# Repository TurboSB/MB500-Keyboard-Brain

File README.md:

# MB500-Keyboard-Brain
 replacement controller for the Korg SP500 with USB MIDI support using a teensy 4.1.

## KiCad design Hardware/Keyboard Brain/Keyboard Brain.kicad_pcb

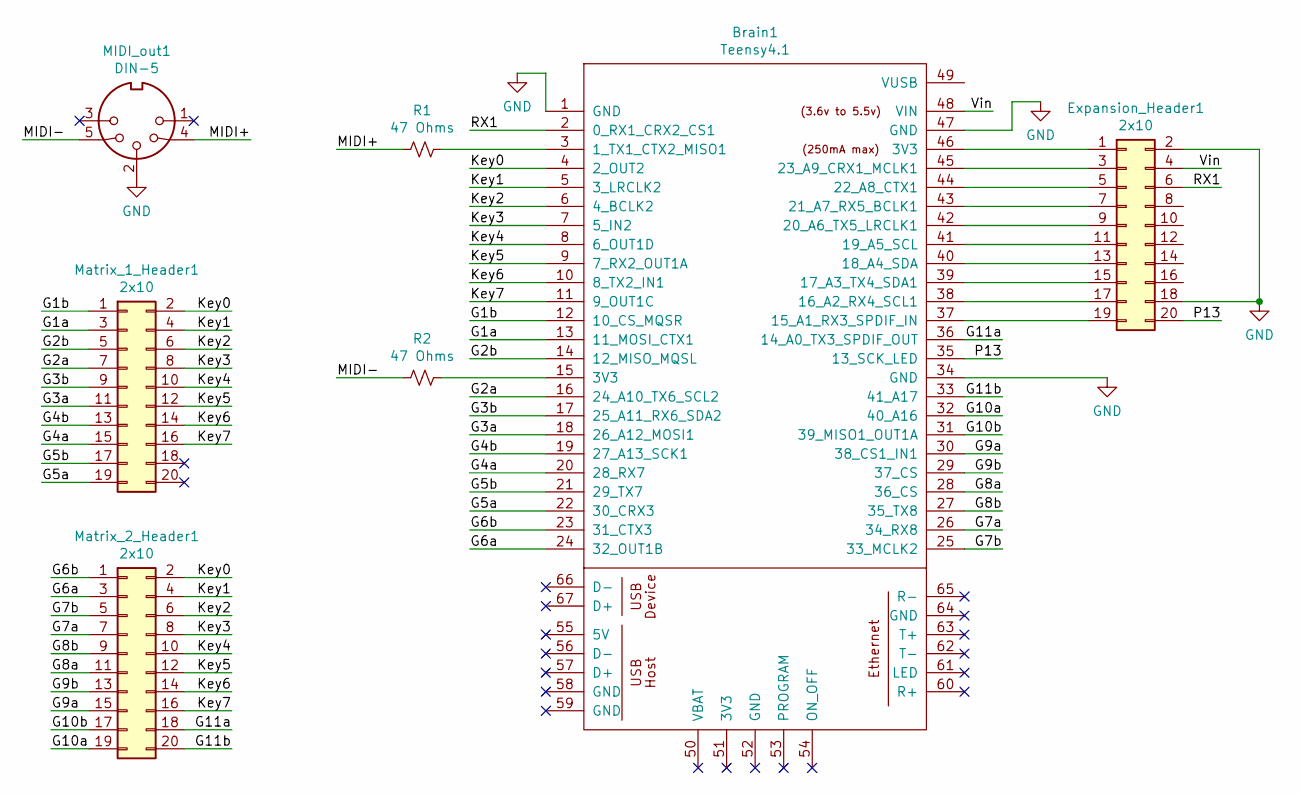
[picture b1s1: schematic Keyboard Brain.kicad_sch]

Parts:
Brain1: Teensy4.1; Teensy41_outer
Expansion_Header1: 2x10; PinHeader_2x10_P2.54mm_Vertical
MIDI_out1: DIN-5; MIDI_DIN5
Matrix_1_Header1, Matrix_2_Header1: 2x10; PinHeader_2x10_P2.54mm_Vertical
R1, R2: 47 Ohms; R_Axial_DIN0411_L9.9mm_D3.6mm_P25.40mm_Horizontal

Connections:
/G1a: Brain1.13 (11_MOSI_CTX1), Matrix_1_Header1.3
/G1b: Brain1.12 (10_CS_MQSR), Matrix_1_Header1.1
/G2a: Brain1.16 (24_A10_TX6_SCL2), Matrix_1_Header1.7
/G2b: Brain1.14 (12_MISO_MQSL), Matrix_1_Header1.5
/G3a: Brain1.18 (26_A12_MOSI1), Matrix_1_Header1.11
/G3b: Brain1.17 (25_A11_RX6_SDA2), Matrix_1_Header1.9
/G4a: Brain1.20 (28_RX7), Matrix_1_Header1.15
/G4b: Brain1.19 (27_A13_SCK1), Matrix_1_Header1.13
/G5a: Brain1.22 (30_CRX3), Matrix_1_Header1.19
/G5b: Brain1.21 (29_TX7), Matrix_1_Header1.17
/G6a: Brain1.24 (32_OUT1B), Matrix_2_Header1.3
/G6b: Brain1.23 (31_CTX3), Matrix_2_Header1.1
/G7a: Brain1.26 (34_RX8), Matrix_2_Header1.7
/G7b: Brain1.25 (33_MCLK2), Matrix_2_Header1.5
/G8a: Brain1.28 (36_CS), Matrix_2_Header1.11
/G8b: Brain1.27 (35_TX8), Matrix_2_Header1.9
/G9a: Brain1.30 (38_CS1_IN1), Matrix_2_Header1.15
/G9b: Brain1.29 (37_CS), Matrix_2_Header1.13
/G10a: Brain1.32 (40_A16), Matrix_2_Header1.19
/G10b: Brain1.31 (39_MISO1_OUT1A), Matrix_2_Header1.17
/G11a: Brain1.36 (14_A0_TX3_SPDIF_OUT), Matrix_2_Header1.18
/G11b: Brain1.33 (41_A17), Matrix_2_Header1.20
/Key0: Brain1.4 (2_OUT2), Matrix_1_Header1.2, Matrix_2_Header1.2
/Key1: Brain1.5 (3_LRCLK2), Matrix_1_Header1.4, Matrix_2_Header1.4
/Key2: Brain1.6 (4_BCLK2), Matrix_1_Header1.6, Matrix_2_Header1.6
/Key3: Brain1.7 (5_IN2), Matrix_1_Header1.8, Matrix_2_Header1.8
/Key4: Brain1.8 (6_OUT1D), Matrix_1_Header1.10, Matrix_2_Header1.10
/Key5: Brain1.9 (7_RX2_OUT1A), Matrix_1_Header1.12, Matrix_2_Header1.12
/Key6: Brain1.10 (8_TX2_IN1), Matrix_1_Header1.14, Matrix_2_Header1.14
/Key7: Brain1.11 (9_OUT1C), Matrix_1_Header1.16, Matrix_2_Header1.16
/MIDI+: MIDI_out1.4, R1.2
/MIDI-: MIDI_out1.5, R2.2
/P13: Brain1.35 (13_SCK_LED), Expansion_Header1.20
/RX1: Brain1.2 (0_RX1_CRX2_CS1), Expansion_Header1.6
/Vin: Brain1.48 (VIN), Expansion_Header1.4
GND: Brain1.1 (GND), Brain1.34 (GND), Brain1.47 (GND), Expansion_Header1.2, Expansion_Header1.18, MIDI_out1.2
unnamed: Brain1.3 (1_TX1_CTX2_MISO1), R1.1
unnamed: Brain1.15 (3V3), R2.1
unnamed: Brain1.37 (15_A1_RX3_SPDIF_IN), Expansion_Header1.19
unnamed: Brain1.38 (16_A2_RX4_SCL1), Expansion_Header1.17
unnamed: Brain1.39 (17_A3_TX4_SDA1), Expansion_Header1.15
unnamed: Brain1.40 (18_A4_SDA), Expansion_Header1.13
unnamed: Brain1.41 (19_A5_SCL), Expansion_Header1.11
unnamed: Brain1.42 (20_A6_TX5_LRCLK1), Expansion_Header1.9
unnamed: Brain1.43 (21_A7_RX5_BCLK1), Expansion_Header1.7
unnamed: Brain1.44 (22_A8_CTX1), Expansion_Header1.5
unnamed: Brain1.45 (23_A9_CRX1_MCLK1), Expansion_Header1.3
unnamed: Brain1.46 (3V3), Expansion_Header1.1

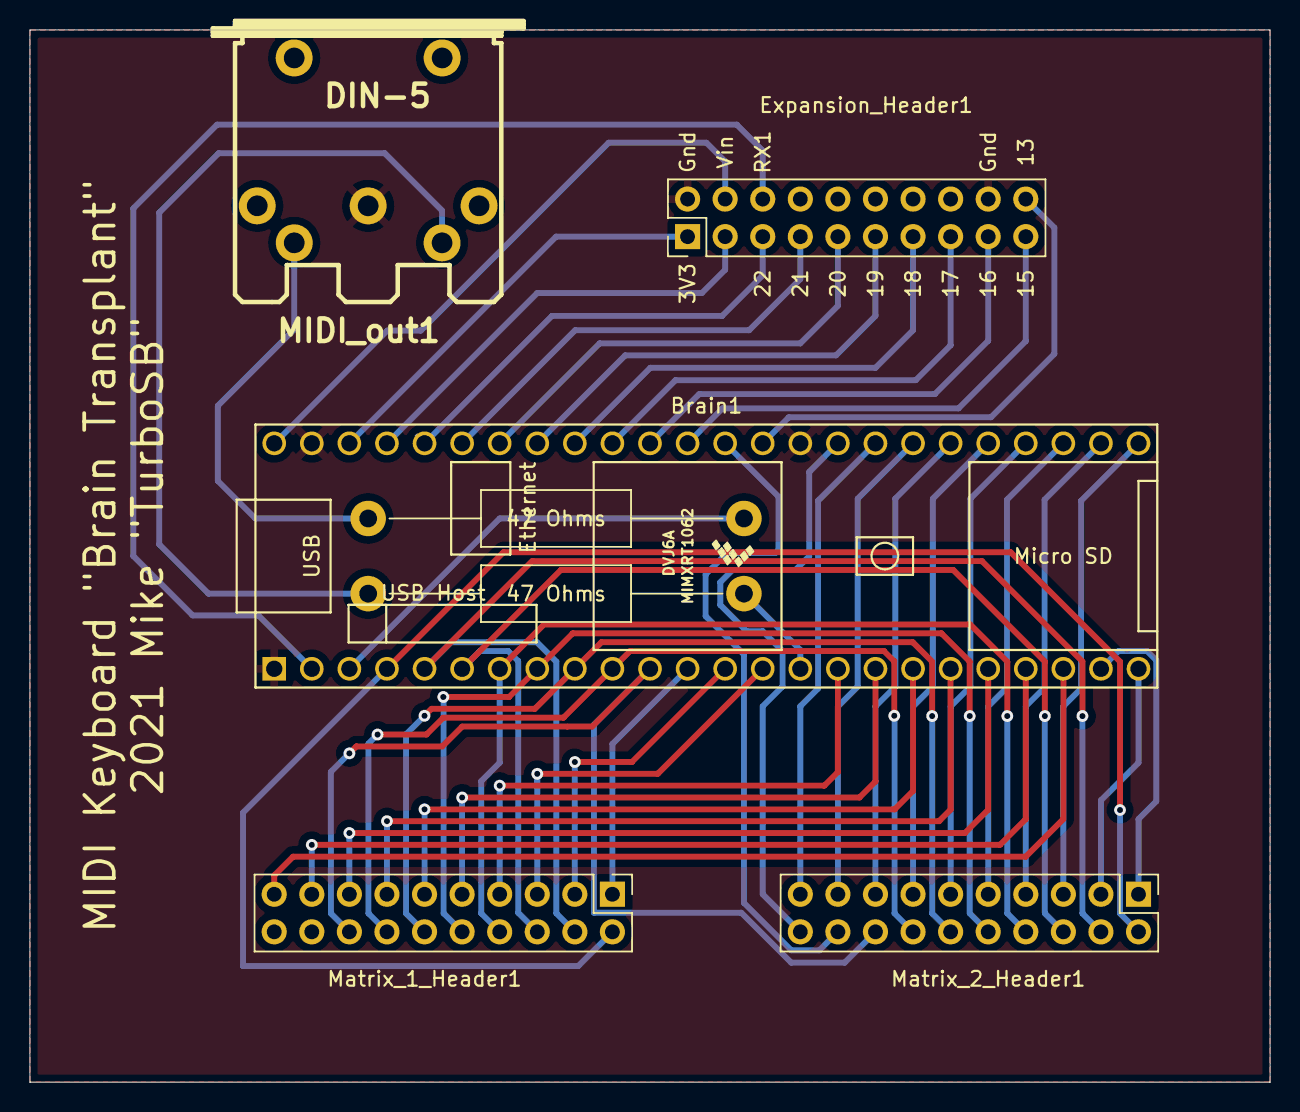
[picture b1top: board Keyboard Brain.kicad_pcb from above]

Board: 2 copper layers, 83.8 x 71.1 mm, 7 parts (0 on the bottom side), 48 nets.

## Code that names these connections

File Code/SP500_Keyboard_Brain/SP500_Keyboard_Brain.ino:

/*  SP500_Keyboard_Brain
    Replacement Controller for Korg SP500 keybed
    Using Teensy 4.1

    written by TurboSB 2021
*/

#include "MultiMap.h"
#include <MIDI.h>

//Setup Midi
MIDI_CREATE_INSTANCE(HardwareSerial, Serial1, MIDI);
const uint8_t channel = 1;

//Key Matrix Pin Assignments
const uint8_t keyPins[8] = {2, 3, 4, 5, 6, 7, 8, 9}; //key 1,2,3,4,5,6,7,8
const uint8_t groupPins[22] = {11, 10, 24, 12, 26, 25, 28, 27, 30, 29, 32, 31, 34, 33, 36, 35, 38, 37, 40, 39, 14, 41}; //{G1a,G1b,G2a,G2b,G3a,G3b,G4a,G4b,G5a,G5b,G6a,G6b,G7a,G7b,G8a,G8b,G9a,G9b,G10a,G1l0b,G11a,G11b}

//Key Matrix Note Values
const uint8_t keys[8][22] = {
  //{G1a,G1b,G2a,G2b,G3a,G3b,G4a,G4b,G5a,G5b,G6a,G6b,G7a,G7b,G8a,G8b,G9a,G9b,G10a,G10b,G11a,G11b}
  {21, 21, 29, 29, 37, 37, 45, 45, 53, 53, 61, 61, 69, 69, 77, 77, 85, 85, 93, 93, 101, 101}, //key1
  {22, 22, 30, 30, 38, 38, 46, 46, 54, 54, 62, 62, 70, 70, 78, 78, 86, 86, 94, 94, 102, 102}, //key2
  {23, 23, 31, 31, 39, 39, 47, 47, 55, 55, 63, 63, 71, 71, 79, 79, 87, 87, 95, 95, 103, 103}, //key3
  {24, 24, 32, 32, 40, 40, 48, 48, 56, 56, 64, 64, 72, 72, 80, 80, 88, 88, 96, 96, 104, 104}, //key3
  {25, 25, 33, 33, 41, 41, 49, 49, 57, 57, 65, 65, 73, 73, 81, 81, 89, 89, 97, 97, 105, 105}, //key5
  {26, 26, 34, 34, 42, 42, 50, 50, 58, 58, 66, 66, 74, 74, 82, 82, 90, 90, 98, 98, 106, 106}, //key6
  {27, 27, 35, 35, 43, 43, 51, 51, 59, 59, 67, 67, 75, 75, 83, 83, 91, 91, 99, 99, 107, 107}, //key7
  {28, 28, 36, 36, 44, 44, 52, 52, 60, 60, 68, 68, 76, 76, 84, 84, 92, 92, 100, 100, 108, 108}, //key8
};

//Damper Pins
const uint8_t damperPin = 16;
const uint8_t damperCC = 64;
bool damperState = false;

//TODO: add adjustable velocity curve
const unsigned long maxTime = 250000; //time at which velocity goes to 0
const unsigned long minTime = 500; //time at which velocity goes to 127
int velocityCurveIn[11] = {0, 4, 8, 16, 18, 29, 42, 64, 80, 105, 127};
int velocityCurveOut[11] = {0, 3, 6, 13, 15, 25, 38, 60, 76, 103, 127};
int velocityMapSize = 11;

//array of times to calculate velocity
unsigned long keyTimes[128];

//array of states of each key (0 = off, 1 = A pressed, 2 = A+B Pressed)
uint8_t keyStates[128];
uint8_t noteStates[128];

bool LED = LOW;

void setup() {
  MIDI.begin();
  //set key pins as inputs
  for (uint8_t i = 0; i < 8; i++)
  {
    pinMode(keyPins[i], INPUT_PULLUP);
  }
  //set group pins as outputs and set them high
  for (uint8_t i = 0; i < 22; i++)
  {
    pinMode(groupPins[i], OUTPUT);
    digitalWrite(groupPins[i], true);
  }
  //set LED as output
  pinMode(13, OUTPUT);
  //set damper pin as input
  pinMode(damperPin, INPUT_PULLUP);
}

void loop() {

  //Arrays to hold key reads
  uint8_t tempA[128], tempB[128];

  //Read keys
  for (uint8_t i = 0; i < 22; i += 2)
  {
    // Read Group A
    digitalWrite(groupPins[i], LOW); //select group
    delayMicroseconds(20); //wait to settle;
    for (uint8_t j = 0; j < 8; j++)
    {
      tempA[keys[j][i]] = !digitalRead(keyPins[j]);
    }
    digitalWrite(groupPins[i], HIGH); //deselect group

    // Read Group B
    digitalWrite(groupPins[i + 1], LOW); //select group
    delayMicroseconds(20); //wait to settle;
    for (uint8_t j = 0; j < 8; j++)
    {
      tempB[keys[j][i + 1]] = !digitalRead(keyPins[j]);
    }
    digitalWrite(groupPins[i + 1], HIGH); //deselect group
  }

  //record time for velocity calc
  unsigned long scanTime = micros();

  for (uint8_t i = 21; i < 109; i++)
  {
    switch (keyStates[i])
    {
      case 0b00:
        if (tempA[i])
        {
          if (tempB[i])
          {
            keyStates[i] = 0b11;
            if (noteStates[i] == 0) {
              noteStates[i]++;
              usbMIDI.sendNoteOn(i, 127, channel);
              MIDI.sendNoteOn(i, 127, channel);
            }
          }
          else
          {
            keyStates[i] = 0b01;
            keyTimes[i] = scanTime;
          }
        }
        else
        {
          if (noteStates[i] > 0)
          {
            noteStates[i]--;
            usbMIDI.sendNoteOff(i, 127, channel);
            MIDI.sendNoteOff(i, 127, channel);
            keyTimes[i] = 0;
          }
        }
        break;
      case 0b01:
        if (tempA[i])
        {
          if (tempB[i] && (noteStates[i] == 0))
          {
            keyStates[i] = 0b11;
            if (noteStates[i] == 0)
            {
              noteStates[i]++;
              unsigned long diff = scanTime - keyTimes[i];
              uint8_t tempVel = map(constrain(diff, 0, maxTime), 0, maxTime, 127, 1);
              tempVel = multiMap<int>(tempVel, velocityCurveIn, velocityCurveOut, velocityMapSize);
              usbMIDI.sendNoteOn(i, tempVel, channel);
              MIDI.sendNoteOn(i, tempVel, channel);
            }
            keyTimes[i] = 0;
          }
        }
        else
        {
          keyStates[i] = 0b00;
          if (noteStates[i] > 0)
          {
            noteStates[i]--;
            unsigned long diff = scanTime - keyTimes[i];
            uint8_t tempVel = map(constrain(diff, 0, maxTime), 0, maxTime, 127, 1);
            tempVel = multiMap<int>(tempVel, velocityCurveIn, velocityCurveOut, velocityMapSize);
            usbMIDI.sendNoteOff(i, tempVel, channel);
            MIDI.sendNoteOff(i, tempVel, channel);
          }
          keyTimes[i] = 0;
        }
        break;
      case 0b11:
        if (tempA[i])
        {
          if (tempB[i])
          {
          }
          else
          {
            keyStates[i] = 0b01;
            keyTimes[i] = scanTime;
          }
        }
        else
        {

          keyStates[i] = 0b00;
          keyTimes[i] = 0;
          if (noteStates[i] > 0)
          {
            noteStates[i]--;
            usbMIDI.sendNoteOff(i, 127, channel);
            MIDI.sendNoteOff(i, 127, channel);
          }
        }
        break;
      default:
        if (noteStates[i] > 0)
        {
          noteStates[i]--;
          keyStates[i] = 0b00;
          keyTimes[i] = 0;
          usbMIDI.sendNoteOff(i, 127, channel);
          MIDI.sendNoteOff(i, 127, channel);
        }
        break;
    }
  }

  bool tempState = digitalRead(damperPin);
  uint8_t tempVal = 0;
  if (tempState != damperState) {
    damperState = tempState;
    if (damperState) {
      tempVal = 127;
    }
    usbMIDI.sendControlChange(damperCC, tempVal, channel);
    MIDI.sendControlChange(damperCC, tempVal, channel);
  }

  // Handle incoming MIDI messages.
  while (usbMIDI.read()) {
  }
}

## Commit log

2022-12-24 Cleanup and add files
